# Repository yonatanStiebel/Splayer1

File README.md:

# Splayer1

<br>

**Splayer1** is a split, wireless, ortholinear, column-staggered, splayed keyboard.

<br>

Each half of the keyboard has 3 rows, 5 columns and 3 extra thumb keys. 

The pinky and ring finger columns are slightly staggered and splayed (hence the name), making for a non-aggressive layout.

The board is choc-spaced, compatible with V1 Kailh Choc switches. 

The keyboard is diodeless and hotswappable, so it can be assembled with minimal solder work. 

The PCB is flippable, and meant to be used for both halves of the keyboard.

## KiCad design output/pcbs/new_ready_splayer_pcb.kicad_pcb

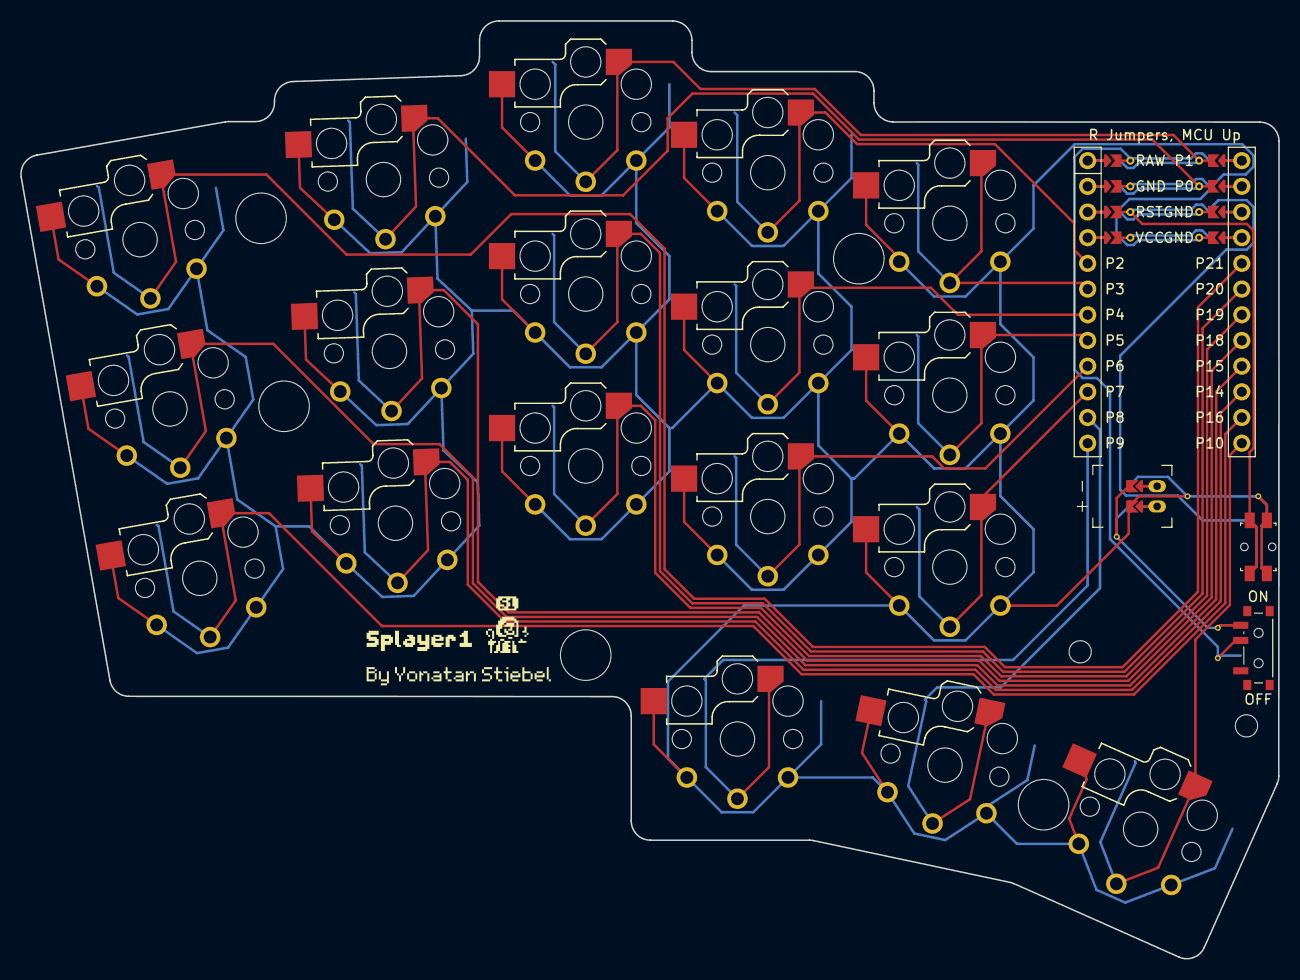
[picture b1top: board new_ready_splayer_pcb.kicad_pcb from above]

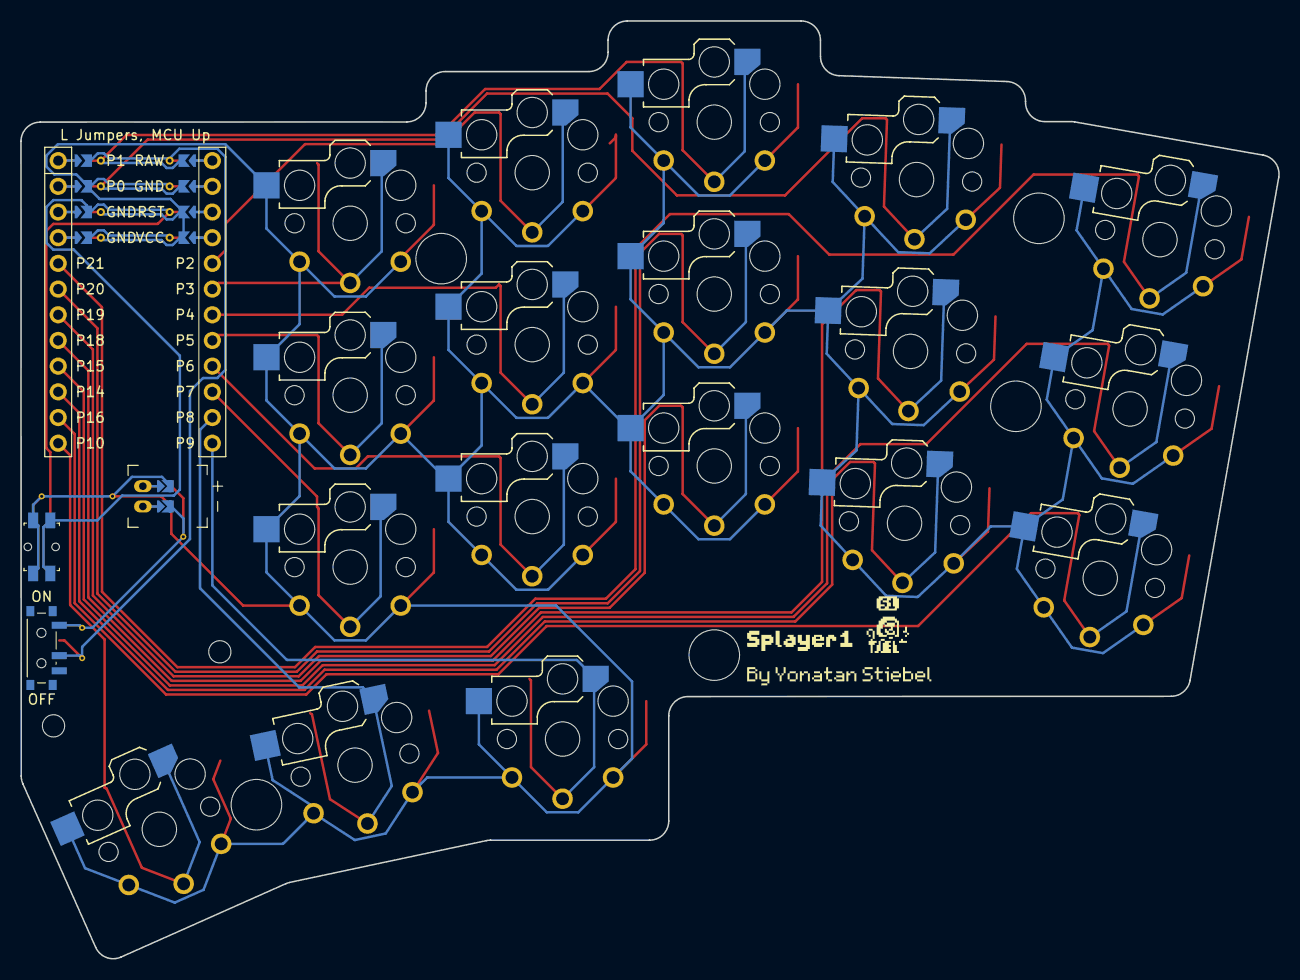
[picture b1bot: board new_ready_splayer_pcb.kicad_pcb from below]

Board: 2 copper layers, 124.4 x 92.7 mm, 29 parts (18 on the bottom side), 24 nets.

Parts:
JST1: battery_connector_jst_ph_2
MCU1: mcu_nice_nano
MH1, MH2, MH3, MH4, MH5, MH6, MH7: mounting_hole_npth
PWR1: power_switch_smd_side
RST1: reset_button_smd_side
S1, S2, S3, S4, S5, S6, S7, S8, S9, S10, S11, S12, S13, S14, S15, S16, S17, S18: switch_choc_v1_v2

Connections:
BAT_P: JST1.1, PWR1.1, PWR1.3
GND: JST1.2, MCU1.3, MCU1.4, MCU1.123, RST1.1, RST1.3, S1.1, S1.2, S2.1, S2.2, S3.1, S3.2, S4.1, S4.2, S5.1, S5.2, S6.1, S6.2, S7.1, S7.2, S8.1, S8.2, S9.1, S9.2, S10.1, S10.2, S11.1, S11.2, S12.1, S12.2, S13.1, S13.2, S14.1, S14.2, S15.1, S15.2, S16.1, S16.2, S17.1, S17.2, S18.1, S18.2
JST1_1: JST1.11, JST1.21, JST1.31
JST1_2: JST1.12, JST1.22, JST1.32
P0: MCU1.2, S6.1, S6.2
P1: MCU1.1, S9.1, S9.2
P2: MCU1.20, S12.1, S12.2
P3: MCU1.19, S15.1, S15.2
P4: MCU1.18, S11.1, S11.2
P5: MCU1.17, S14.1, S14.2
P6: MCU1.16, S10.1, S10.2
P7: MCU1.15, S13.1, S13.2
P8: MCU1.14, S17.1, S17.2
P9: MCU1.13, S16.1, S16.2
P10: MCU1.12, S18.1, S18.2
P14: MCU1.10, S4.1, S4.2
P15: MCU1.9, S2.1, S2.2
P16: MCU1.11, S1.1, S1.2
P18: MCU1.8, S5.1, S5.2
P19: MCU1.7, S7.1, S7.2
P20: MCU1.6, S8.1, S8.2
P21: MCU1.5, S3.1, S3.2
RAW: MCU1.124, PWR1.2
RST: MCU1.122, RST1.2, RST1.4

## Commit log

2024-04-24 tryoing to commit files
2024-04-24 Update README.md
    added initial description of the keyboard
2024-04-24 added logo
2024-04-24 added logo to README
2024-04-25 updated footprints to ceoloide footprints
2024-04-25 switched to ceoloide mounting hole frootprints, and designated a folder for ceoloide footprints to be consistent with the website. flushed the MCU against the inner wall of the case
2024-04-25 updated README file
2024-04-27 redefined mounting holes positions
2024-04-27 added routed pcb
2024-04-28 designed a new plate case for the keyboard
2024-04-28 formated README file
2024-04-28 added more information about the keyboard in the README file
2024-04-29 added gerber folder and the final case stl file
2024-05-06 redesigned the PCB to avoid errors, removed choc v2 support
2024-05-06 drilled holes for reset side buttons
2024-05-06 updated README files and images
2024-05-09 added seperate stl fiiles for the case
